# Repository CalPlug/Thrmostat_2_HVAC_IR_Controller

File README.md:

# ThermostatControl
Jigar Hira

Navid Bazmoon

Code to interface the NEST thermostat with ESP32

Utilizes the RMT ESP32 library to send IR signals controlling a portable AC unit.

## IR Transmission
ESP32 has built-in hardware for handling IR Codes.
The RMT library feeds the hardware two signals:

1)	Data signal which represents the 0 and 1 bits
2)	Carrier frequency square wave

The hardware in the ESP32 modulates the data signal using the square wave to produce the IR signal (more information can be found here: https://docs.espressif.com/projects/esp-idf/en/latest/api-reference/peripherals/rmt.html).

## NEST signals
In order to interface with the NEST smart thermostat, we use a simple circuit to convert 24VAC thermostat signals to lower voltage DC signals.

This allows us to use the GPIO pins on the ESP32 to detect what the NEST has turned on or off.

### NOTE:
This project is still in development

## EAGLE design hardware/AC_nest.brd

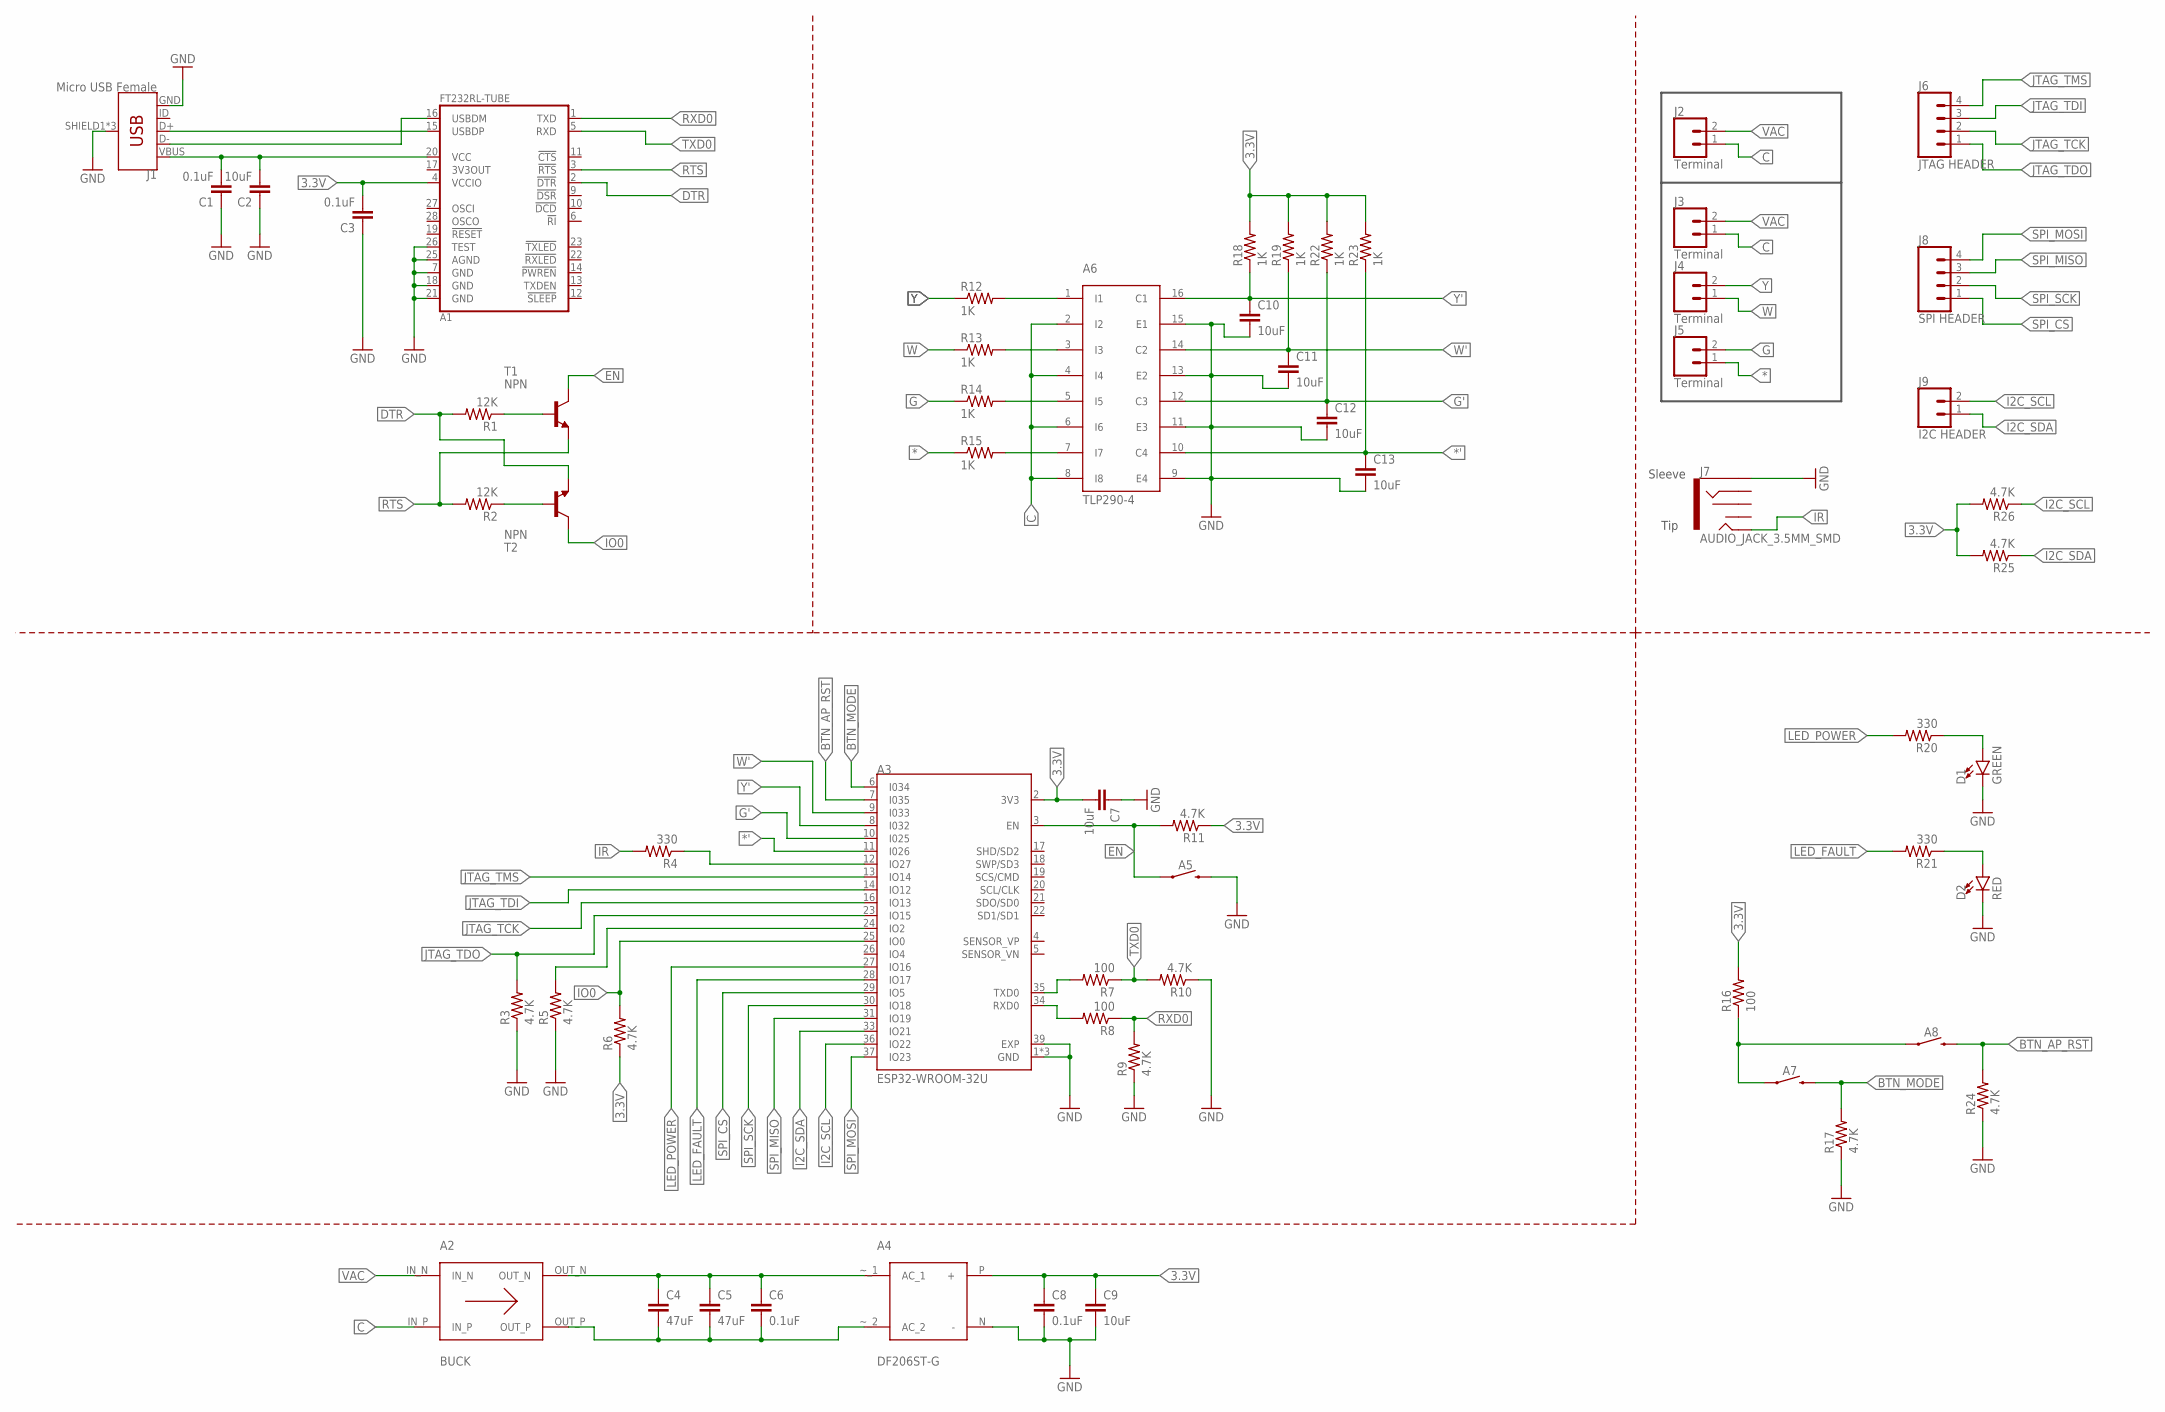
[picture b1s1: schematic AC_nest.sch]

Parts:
A1: FT232RL; SSOP28-LD
A2: BUCK
A3: ESP32-WROOM-32U; XCVR_ESP32-WROOM-32U
A4: DF206ST-G
A5, A7, A8: TL3302AF180QJ
A6: TLP290-4
C1, C3, C6, C8: 0.1uF; C0603
C2, C7, C9, C10, C11, C12, C13: 10uF; C0603
C4, C5: 47uF; C0603
D1: GREEN; LED-0603
D2: RED; LED-0603
J1: Micro USB Female; USB-B-MICRO-SMD
J2, J3, J4, J5: Terminal; SCREWTERMINAL-3.5MM-2
J6: JTAG HEADER; 1X04
J7: AUDIO_JACK_3.5MM_SMD; AUDIO-JACK-3.5MM-SMD
J8: SPI HEADER; 1X04
J9: I2C HEADER; 1X02
R1, R2: 12K; R0603
R3, R5, R6, R9, R10, R11, R17, R24, R25, R26: 4.7K; R0603
R4, R20, R21: 330; R0603
R7, R8, R16: 100; R0603
R12, R13, R14, R15, R18, R19, R22, R23: 1K; R0603
T1, T2: NPN; SOT23-EBC

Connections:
3.3V: A1.4 (VCCIO), A3.2 (3V3), A4.P (+), C3.2, C7.2, C8.1, C9.1, R6.1, R11.1, R16.2, R18.2, R19.2, R22.2, R23.2, R25.2, R26.2
3V3OUT: A1.17 (3V3OUT)
*: J5.1, R15.1
*': A3.11 (I026), A6.10 (C4), C13.1, R23.1
BTN_AP_RST: A3.7 (I035), A8.2, R24.2
BTN_MODE: A3.6 (I034), A7.2, R17.2
C: A2.IN_P, A6.2 (I2), A6.4 (I4), A6.6 (I6), A6.8 (I8), J2.1, J3.1
DTR: A1.2 (!DTR), R1.2, T2.E
EN: A3.3 (EN), A5.1, R11.2, T1.C
G: J5.2, R14.1
G': A3.10 (I025), A6.12 (C3), C12.1, R22.1
GND: A1.7 (GND), A1.18 (GND), A1.21 (GND), A1.25 (AGND), A1.26 (TEST), A3.1 (GND), A3.15 (GND), A3.38 (GND), A3.39 (EXP), A4.N (-), A5.2, A6.9 (E4), A6.11 (E3), A6.13 (E2), A6.15 (E1), C1.1, C2.1, C3.1, C7.1, C8.2, C9.2, C10.2, C11.2, C12.2, C13.2, D1.C, D2.C, J1.GND, J1.SHIELD1 (SHIELD), J1.SHIELD2 (SHIELD), J1.SHIELD3 (SHIELD), J7.SLEEVE, R3.1, R5.1, R9.1, R10.1, R17.1, R24.1
I2C_SCL: A3.36 (IO22), J9.2, R26.1
I2C_SDA: A3.33 (IO21), J9.1, R25.1
IO0: A3.25 (IO0), R6.2, T2.C
IR: J7.TIP, R4.2
JTAG_TCK: A3.16 (IO13), J6.2
JTAG_TDI: A3.14 (IO12), J6.3
JTAG_TDO: A3.23 (IO15), J6.1, R3.2
JTAG_TMS: A3.13 (IO14), J6.4
LED_FAULT: A3.28 (IO17), R21.2
LED_POWER: A3.27 (IO16), R20.2
unnamed: A6.1 (I1), R12.2
unnamed: A6.3 (I3), R13.2
unnamed: A6.5 (I5), R14.2
unnamed: A6.7 (I7), R15.2
unnamed: A3.34 (RXD0), R8.2
unnamed: A3.24 (IO2), R5.2
unnamed: A3.12 (IO27), R4.1
unnamed: A1.15 (USBDP), J1.D+
unnamed: A3.35 (TXD0), R7.2
unnamed: A1.16 (USBDM), J1.D-
unnamed: A2.OUT_N, A4.~_1 (AC_1), C4.1, C5.1, C6.1
unnamed: R2.1, T2.B
unnamed: A2.OUT_P, A4.~_2 (AC_2), C4.2, C5.2, C6.2
unnamed: R1.1, T1.B
unnamed: D1.A, R20.1
unnamed: D2.A, R21.1
unnamed: A7.1, A8.1, R16.1
RTS: A1.3 (!RTS), R2.2, T1.E
RXD0: A1.1 (TXD), R8.1, R9.2
SPI_CS: A3.29 (IO5), J8.1
SPI_MISO: A3.31 (IO19), J8.3
SPI_MOSI: A3.37 (IO23), J8.4
SPI_SCK: A3.30 (IO18), J8.2
TXD0: A1.5 (RXD), R7.1, R10.2
USB_VBUS: A1.20 (VCC), C1.2, C2.2, J1.VBUS
VAC: A2.IN_N, J2.2, J3.2
W: J4.1, R13.1
W': A3.9 (I033), A6.14 (C2), C11.1, R19.1
Y: J4.2, R12.1
Y': A3.8 (I032), A6.16 (C1), C10.1, R18.1

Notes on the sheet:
Sleeve
Tip

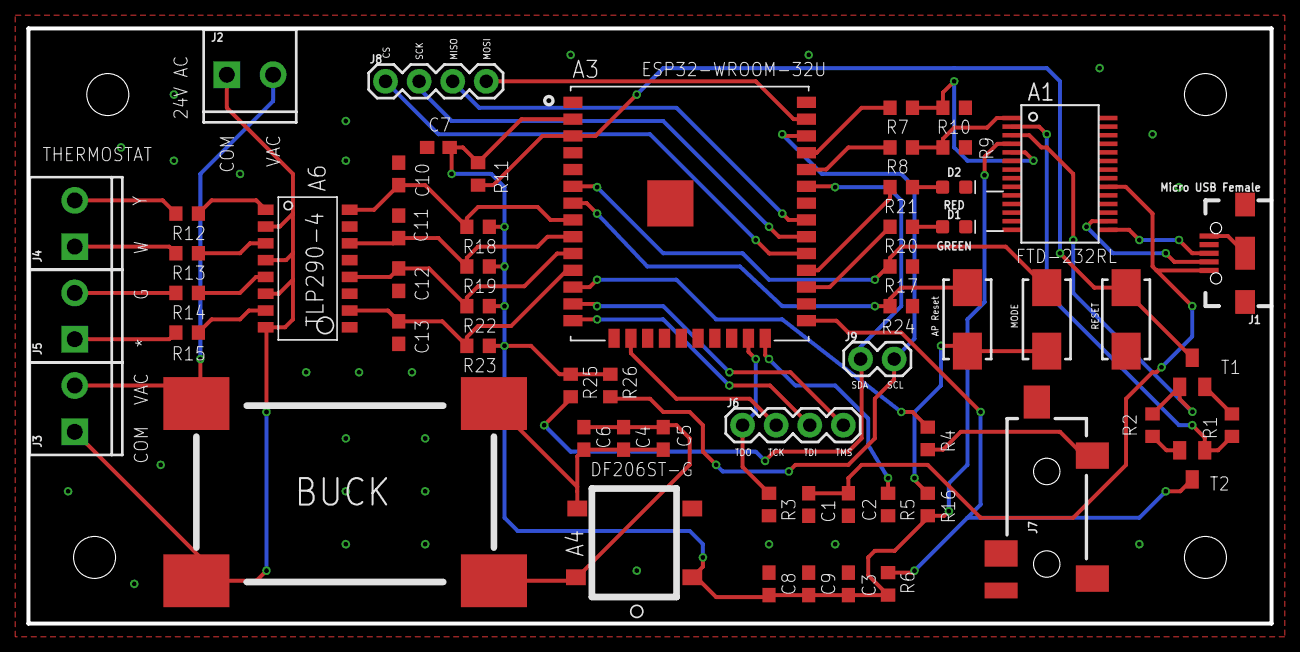
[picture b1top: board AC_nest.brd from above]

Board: 2 copper layers, 94.0 x 45.0 mm, 60 parts (0 on the bottom side), 51 nets.

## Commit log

2019-03-04 Update file structure
2019-08-15 update to public
2019-08-16 fixed readme

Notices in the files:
parts and their libraries:
SparkFun-LED: Licensing: Creative Commons ShareAlike 4.0 International - https://creativecommons.org/licenses/by-sa/4.0
